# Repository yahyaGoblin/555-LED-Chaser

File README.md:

# 555 LED Chaser

A LED Chaser build with help of Guide in Hack Club Stasis
As a first-year university student, I have not worked on any hardware-based projects yet, so I wanted to experience PCB design and face its challenges

---

## 🧾 Bill of Materials (BOM)

---

## 🧩 PCB Cost

| Source | Cost      |
| ------ | --------- |
| Seeed Studio | 12.35 USD |

---

## 🙌 Credits

* Hack Club Stasis
* Tutorial by Tanishq Goyal & CAN

---

## ⭐ Status

✅ Completed
🟢 Ready for fabrication

---

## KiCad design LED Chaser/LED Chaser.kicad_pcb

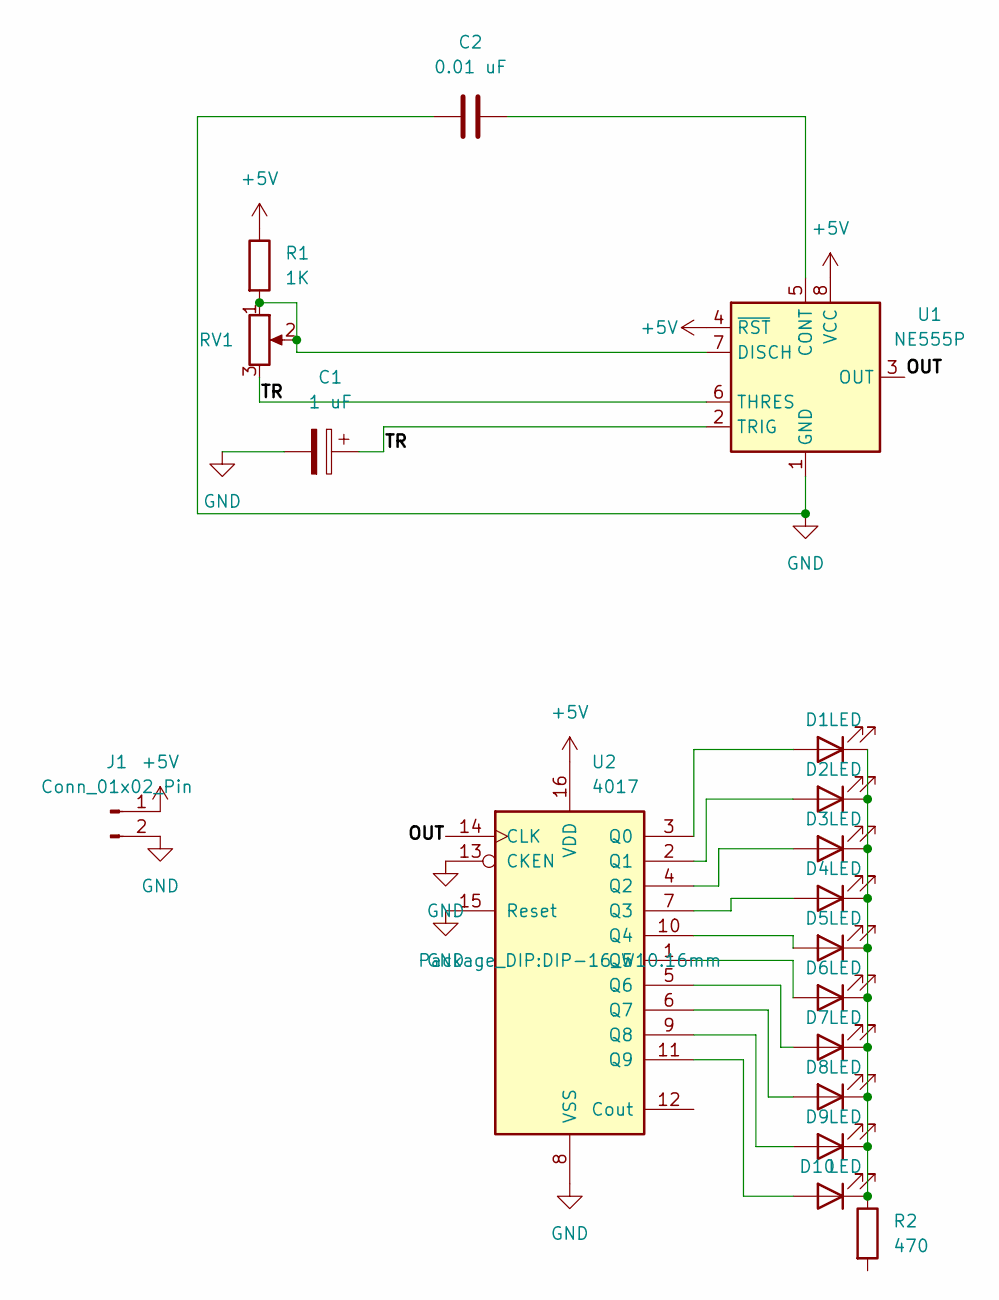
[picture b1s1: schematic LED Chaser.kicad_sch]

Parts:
C1: 1 uF; CP_Radial_D5.0mm_P2.50mm
C2: 0.01 uF; C_Disc_D5.0mm_W2.5mm_P5.00mm
D1, D2, D3, D4, D5, D6, D7, D8, D9, D10: LED; LED_D5.0mm
J1: Conn_01x02_Pin; PinHeader_1x02_P2.54mm_Vertical
R1: 1K; R_Axial_DIN0207_L6.3mm_D2.5mm_P10.16mm_Horizontal
R2: 470; R_Axial_DIN0207_L6.3mm_D2.5mm_P10.16mm_Horizontal
RV1: 50K; Potentiometer_Bourns_3386P_Vertical
U1: NE555P; DIP-8_W7.62mm
U2: 4017; DIP-16_W10.16mm

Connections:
+5V: J1.1, R1.1, U1.4 (~RST), U1.8 (VCC), U2.16 (VDD)
/OUT: U1.3 (OUT), U2.14 (CLK)
/TR: C1.1, RV1.3, U1.2 (TRIG), U1.6 (THRES)
GND: C1.2, C2.1, J1.2, U1.1 (GND), U2.8 (VSS), U2.13 (CKEN), U2.15 (Reset)
unnamed: D1.2 (A), U2.3 (Q0)
unnamed: D1.1 (K), D2.1 (K), D3.1 (K), D4.1 (K), D5.1 (K), D6.1 (K), D7.1 (K), D8.1 (K), D9.1 (K), D10.1 (K), R2.1
unnamed: D2.2 (A), U2.2 (Q1)
unnamed: D3.2 (A), U2.4 (Q2)
unnamed: D4.2 (A), U2.7 (Q3)
unnamed: D5.2 (A), U2.10 (Q4)
unnamed: D6.2 (A), U2.1 (Q5)
unnamed: D7.2 (A), U2.5 (Q6)
unnamed: D8.2 (A), U2.6 (Q7)
unnamed: D9.2 (A), U2.9 (Q8)
unnamed: D10.2 (A), U2.11 (Q9)
unnamed: C2.2, U1.5 (CONT)
unnamed: R1.2, RV1.1, RV1.2, U1.7 (DISCH)

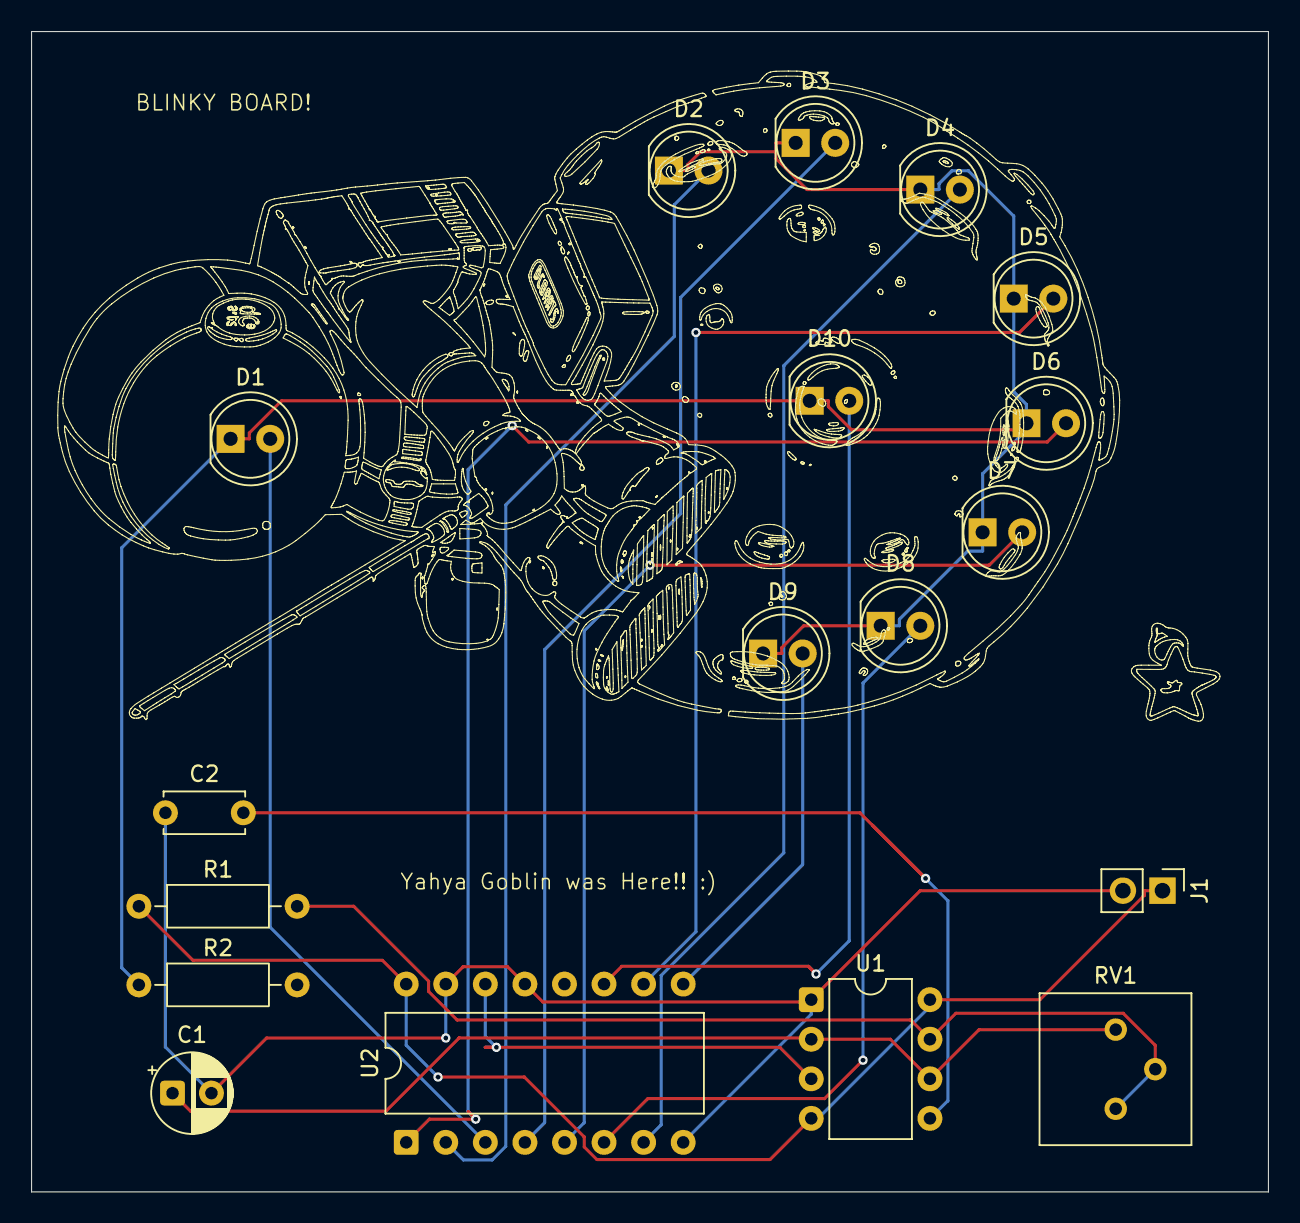
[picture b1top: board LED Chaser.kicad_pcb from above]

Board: 2 copper layers, 79.4 x 74.5 mm, 18 parts (0 on the bottom side), 17 nets.

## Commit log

2026-04-01 Enhance README with project details and images
    Added images and improved project description.
2026-04-01 Enhance README
    Added personal context about the project experience.
2026-04-07 Update README with BOM
    Added a Bill of Materials (BOM) and PCB cost details.
2026-04-07 Update headings in README.md for consistency
2026-04-07 Refactor README with tables and additional sections
    Updated the Bill of Materials and PCB Cost sections to use tables for better readability. Added a Credits and Status section.
2026-04-09 Remove Bill of Materials and cost details
    Removed the Bill of Materials section and its associated cost from the README.
2026-04-10 Modify PCB cost and update image in README
    Updated PCB cost information and replaced an image.
